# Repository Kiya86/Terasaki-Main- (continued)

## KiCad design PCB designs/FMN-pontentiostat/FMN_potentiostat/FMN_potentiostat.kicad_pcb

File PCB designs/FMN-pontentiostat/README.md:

# FMN
This repository includes the KiCad PCB design for FMN detection, embedded firmware for hardware control, and an Android application for wireless communication, data acquisition, and system integration.”

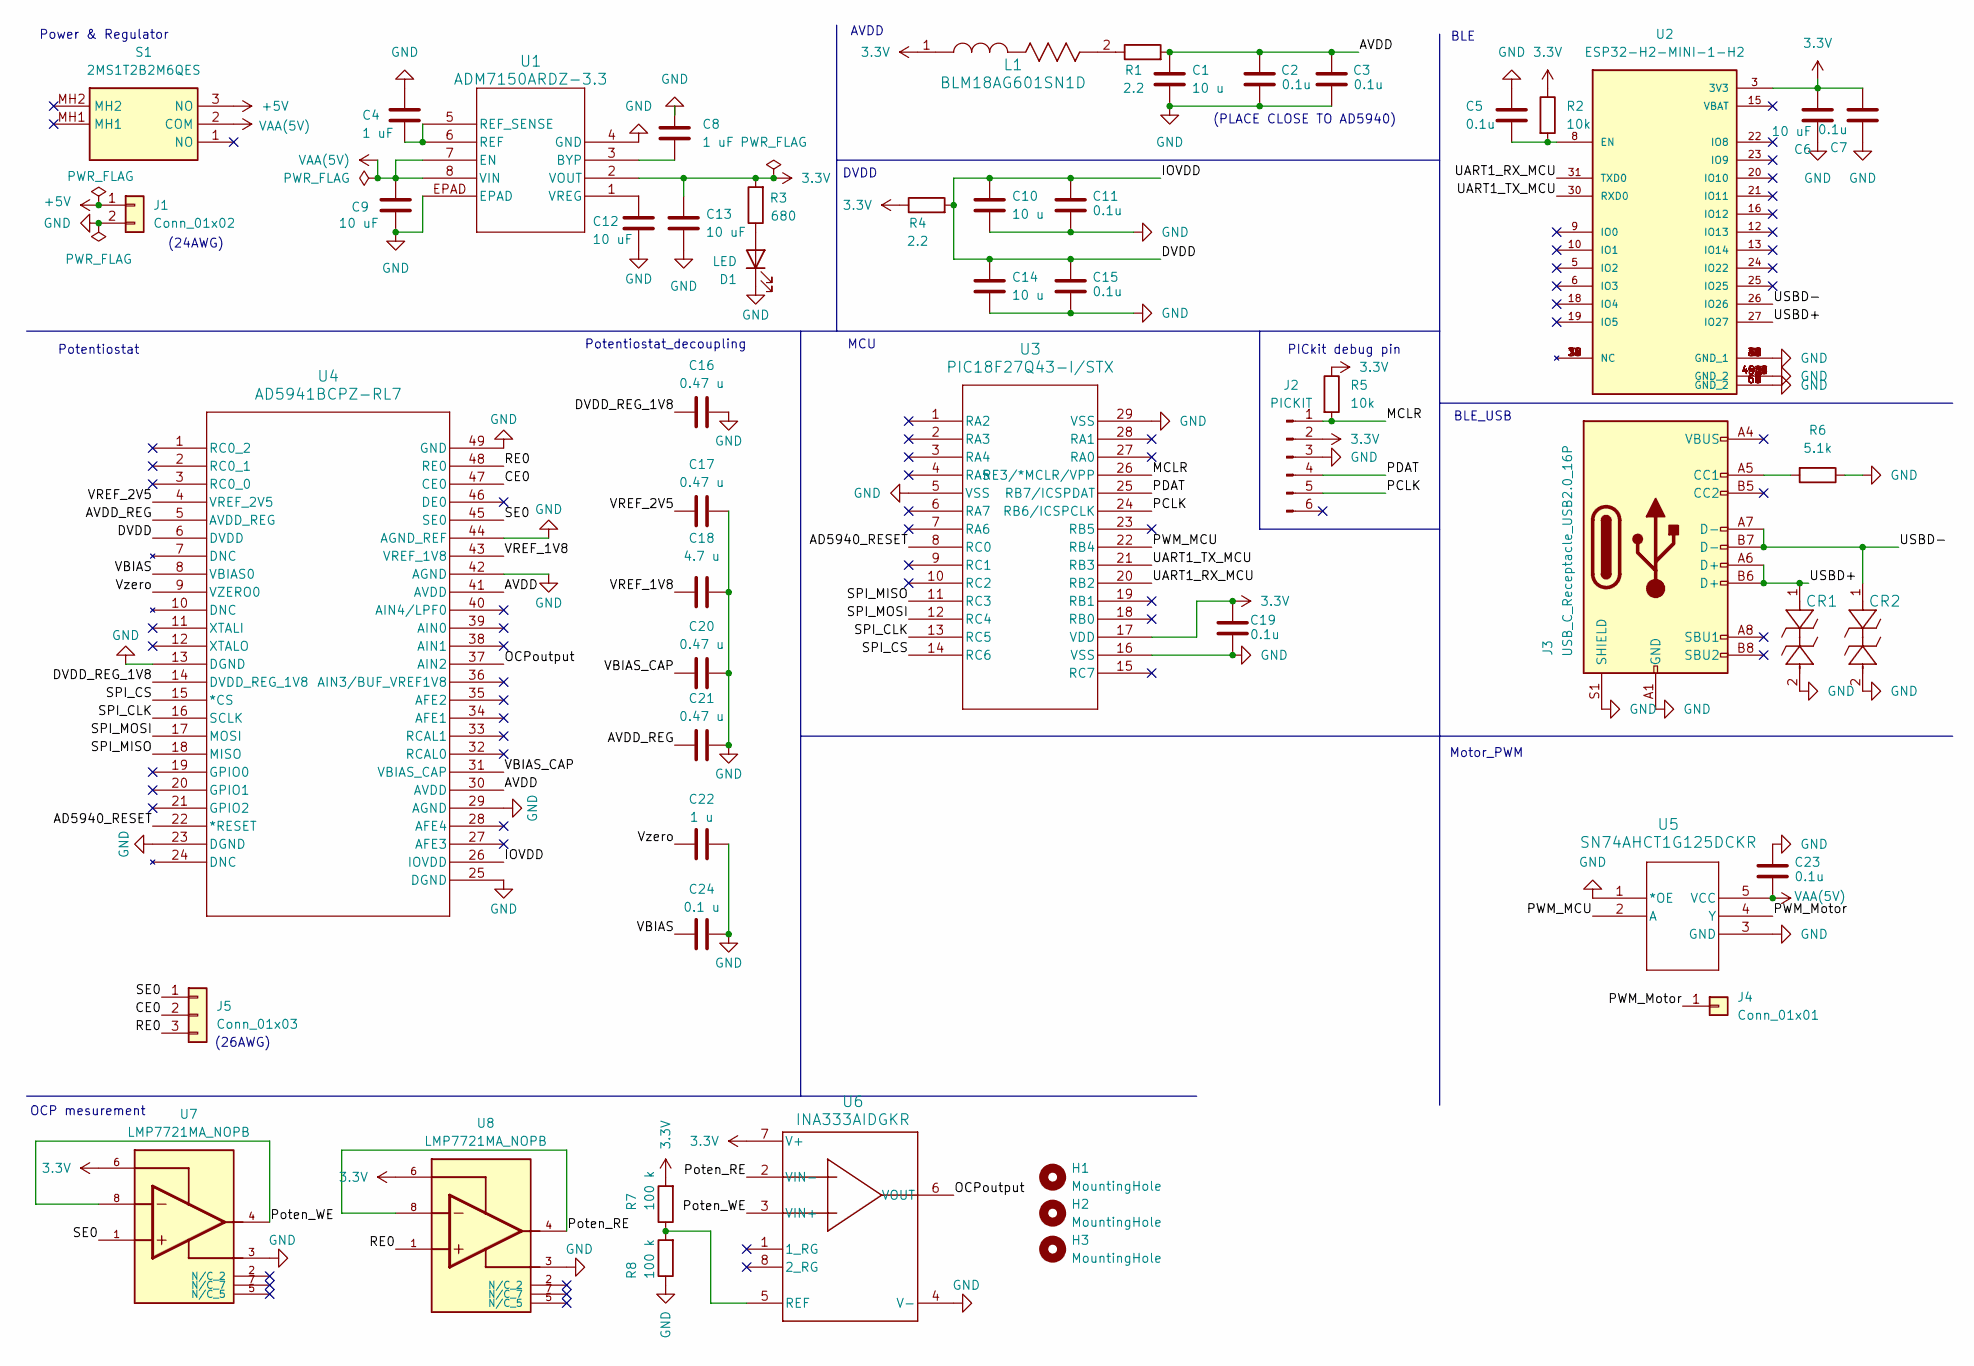
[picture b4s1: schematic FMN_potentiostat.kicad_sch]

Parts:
C1, C10, C14: 10 u; C_0805_2012Metric; MfgPN CL21B106KPQNNNE
C2, C3, C5, C7, C11, C15, C19, C23: 0.1u; C_0603_1608Metric; MfgPN GRM188R71H104KA93D
C4, C8: 1 uF; C_0603_1608Metric; MfgPN CL10B105KP8NNNC
C6, C9, C12, C13: 10 uF; C_0805_2012Metric; MfgPN CL21B106KPQNNNE
C16, C17, C20, C21: 0.47 u; C_0402_1005Metric; MfgPN CC0402KRX5R6BB474
C18: 4.7 u; C_0603_1608Metric; MfgPN CL10A475KP8NNNC
C22: 1 u; C_0402_1005Metric; MfgPN CL05A105KP5NNNC
C24: 0.1 u; C_0402_1005Metric; MfgPN CC0402KRX7R6BB104
CR1, CR2: LESD5D5.0CT1G; D_SOD-523; MfgPN LESD5D5.0CT1G
D1: LED; LED_0201_0603Metric; MfgPN XL-0201SURC
H1, H2, H3: MountingHole; MountingHole_3.2mm_M3
J1: Conn_01x02; Molex_Nano-Fit_105309-xx02_1x02_P2.50mm_Vertical; MfgPN 1053091202
J2: PICKIT; Molex_KK-254_AE-6410-06A_1x06_P2.54mm_Vertical; MfgPN 22272061
J3: USB_C_Receptacle_USB2.0_16P; USB_C_Receptacle_Molex_105450-0101; MfgPN 1054500101
J4: Conn_01x01; PinHeader_1x01_P2.54mm_Vertical; MfgPN A254N01-0B1P51-H25A60
J5: Conn_01x03; Molex_Nano-Fit_105309-xx03_1x03_P2.50mm_Vertical; MfgPN 1053091203
L1: BLM18AG601SN1D; FILTER_BLM18AG_MUR; MfgPN BLM18AG601SN1D
R1, R4: 2.2; R_0402_1005Metric; MfgPN RC0402FR-072R2L
R2, R5: 10k; R_Axial_DIN0207_L6.3mm_D2.5mm_P2.54mm_Vertical; MfgPN MBB02070C1002FCT00
R3: 680; R_0201_0603Metric; MfgPN RC0201FR-07680RL
R6: 5.1k; R_0603_1608Metric; MfgPN RC0603FR-075K1L
R7, R8: 100 k; R_0402_1005Metric; MfgPN RC0402FR-07100KL
S1: 2MS1T2B2M6QES; Mouser Part Number 118-2MS1T2B2M6QES
U1: ADM7150ARDZ-3.3; RD_8_2_ADI; MfgPN ADM7150ARDZ-3.3-R7
U2: ESP32-H2-MINI-1-H2; MODULE_ESP32-H2-MINI-1-H2; PARTREV v0.5
U3: PIC18F27Q43-I/STX; VQFN28_STX_MCH; MfgPN PIC18F27Q43-I/STX
U4: AD5941BCPZ-RL7; CP-48-4_ADI; MfgPN AD5941BCPZ-RL7
U5: SN74AHCT1G125DCKR; DCK5; MfgPN SN74AHCT1G125DCKR
U6: INA333AIDGKR; DGK0008A-MFG; MfgPN INA333AIDGKR
U7, U8: LMP7721MA_NOPB; SOIC127P599X175-8N; PARTREV E

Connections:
3.3V: C6.2, C7.2, C13.1, C19.2, J2.2, L1.1, R2.1, R3.2, R4.1, R5.1, R7.2, U1.2 (VOUT), U2.3 (3V3), U3.17 (VDD), U6.7 (V+), U7.6, U8.6
+5V: J1.1, S1.3 (NO)
/AD5940_RESET: U3.8 (RC0), U4.22 (*RESET)
/AVDD: C1.1, C2.2, C3.2, R1.2, U4.30 (AVDD), U4.41 (AVDD)
/AVDD_REG: C21.1, U4.5 (AVDD_REG)
/CE0: J5.2, U4.47 (CE0)
/DVDD: C10.1, C11.2, C14.1, C15.2, R4.2, U4.6 (DVDD), U4.26 (IOVDD)
/DVDD_REG_1V8: C16.1, U4.14 (DVDD_REG_1V8)
/MCLR: J2.1, R5.2, U3.26 (RE3/*MCLR/VPP)
/OCPoutput: U4.37 (AIN2), U6.6 (VOUT)
/PCLK: J2.5, U3.24 (RB6/ICSPCLK)
/PDAT: J2.4, U3.25 (RB7/ICSPDAT)
/PWM_MCU: U3.22 (RB4), U5.2 (A)
/PWM_Motor: J4.1, U5.4 (Y)
/Poten_RE: U6.2 (VIN-), U8.4, U8.8
/Poten_WE: U6.3 (VIN+), U7.4, U7.8
/RE0: J5.3, U4.48 (RE0), U8.1
/SE0: J5.1, U4.45 (SE0), U7.1
/SPI_CLK: U3.13 (RC5), U4.16 (SCLK)
/SPI_CS: U3.14 (RC6), U4.15 (*CS)
/SPI_MISO: U3.11 (RC3), U4.18 (MISO)
/SPI_MOSI: U3.12 (RC4), U4.17 (MOSI)
/UART1_RX_MCU: U2.31 (TXD0), U3.20 (RB2)
/UART1_TX_MCU: U2.30 (RXD0), U3.21 (RB3)
/USBD+: CR1.1, J3.A6 (D+), J3.B6 (D+), U2.27 (IO27)
/USBD-: CR2.1, J3.A7 (D-), J3.B7 (D-), U2.26 (IO26)
/VBIAS: C24.1, U4.8 (VBIAS0)
/VBIAS_CAP: C20.1, U4.31 (VBIAS_CAP)
/VREF_1V8: C18.2, U4.43 (VREF_1V8)
/VREF_2V5: C17.1, U4.4 (VREF_2V5)
/Vzero: C22.1, U4.9 (VZERO0)
GND: C1.2, C2.1, C3.1, C4.1, C5.1, C6.1, C7.1, C8.1, C9.2, C10.2, C11.1, C12.2, C13.2, C14.2, C15.1, C16.2, C17.2, C18.1, C19.1, C20.2, C21.2, C22.2, C23.2, C24.2, CR1.2, CR2.2, D1.1 (K), J1.2, J2.3, J3.A1 (GND), J3.A12 (GND), J3.B1 (GND), J3.B12 (GND), J3.S1 (SHIELD), R6.1, R8.1, U1.4 (GND), U1.EPAD, U2.1 (GND_1), U2.2 (GND_1), U2.11 (GND_1), U2.14 (GND_1), U2.36 (GND_1), U2.37 (GND_1), U2.38 (GND_1), U2.39 (GND_1), U2.40 (GND_1), U2.41 (GND_1), U2.42 (GND_1), U2.43 (GND_1), U2.44 (GND_1), U2.45 (GND_1), U2.46 (GND_1), U2.47 (GND_2), U2.48 (GND_2), U2.49_1 (GND_2), U2.49_2 (GND_2), U2.49_3 (GND_2), U2.49_4 (GND_2), U2.49_5 (GND_2), U2.49_6 (GND_2), U2.49_7 (GND_2), U2.49_8 (GND_2), U2.49_9 (GND_2), U2.50 (GND_2), U2.51 (GND_2), U2.52 (GND_2), U2.53 (GND_2), U2.54 (GND_2), U2.55 (GND_2), U2.56 (GND_2), U2.57 (GND_2), U2.58 (GND_2), U2.59 (GND_2), U2.60 (GND_2), U2.61 (GND_2), U2.62 (GND_2), U2.63 (GND_2), U2.64 (GND_2), U2.65 (GND_2), U3.5 (VSS), U3.16 (VSS), U3.29 (VSS), U4.13 (DGND), U4.23 (DGND), U4.25 (DGND), U4.29 (AGND), U4.42 (AGND), U4.44 (AGND_REF), U4.49 (GND), U5.1 (*OE), U5.3 (GND), U6.4 (V-), U7.3, U8.3
unnamed: D1.2 (A), R3.1
unnamed: J3.A5 (CC1), R6.2
unnamed: L1.2, R1.1
unnamed: C8.2, U1.3 (BYP)
unnamed: C4.2, U1.5 (REF_SENSE), U1.6 (REF)
unnamed: C12.1, U1.1 (VREG)
unnamed: C5.2, R2.2, U2.8 (EN)
unnamed: R7.1, R8.2, U6.5 (REF)
VAA(5V): C9.1, C23.1, S1.2 (COM), U1.7 (EN), U1.8 (VIN), U5.5 (VCC)

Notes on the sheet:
AVDD
BLE
Motor_PWM
(PLACE CLOSE TO AD5940)
(24AWG)
MCU
Potentiostat
PICkit debug pin
Power & Regulator
DVDD
OCP mesurement
Potentiostat_decoupling
BLE_USB
(26AWG)

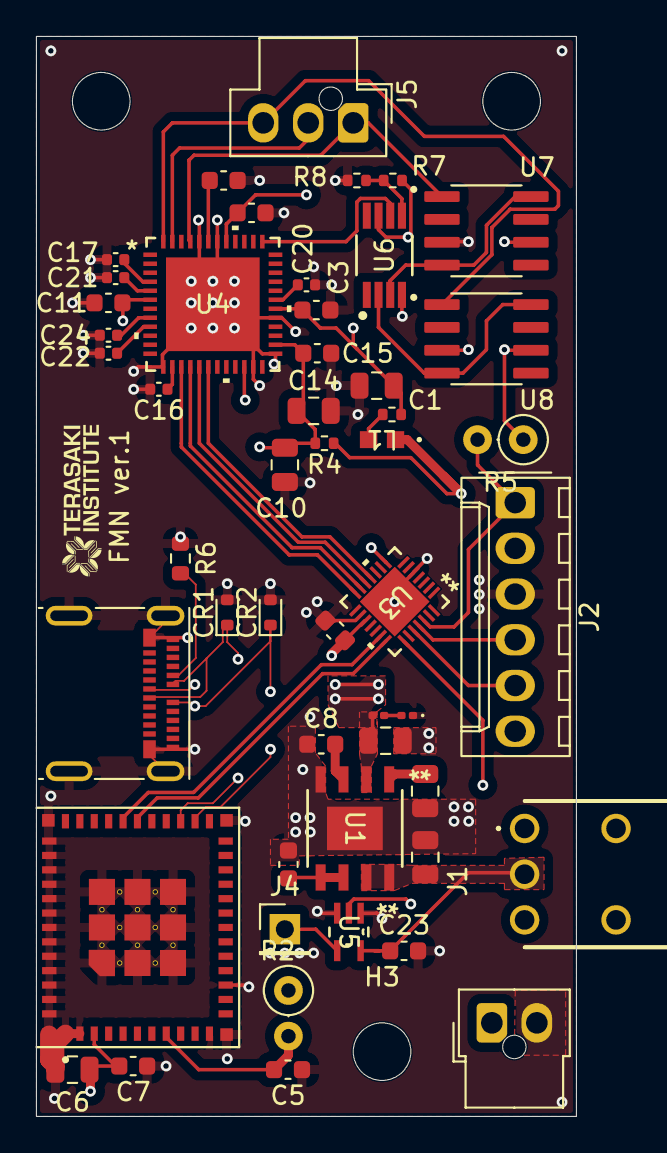
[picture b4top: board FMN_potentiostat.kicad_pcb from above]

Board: 4 copper layers, 30.0 x 60.0 mm, 53 parts (0 on the bottom side), 41 nets.

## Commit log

2026-05-07 Create s
2026-05-12 minwoo update
2026-05-13 051226
2026-05-14 measurement time fixed for ResearchDashboard
2026-05-16 FMN sensor PCB design
2026-05-16 FMN PCB design upload
2026-05-20 Todo list updated with due dates
2026-05-25 Create Comments for PCB
2026-06-03 Flexible PCB schematic
